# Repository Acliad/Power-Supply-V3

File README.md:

This project is for a constant voltage/constant current DC power supply designed by me. The project initially started as a way to learn more about electronics, and it served that purpose extremely well. There are many improvements that could be made, but those will probably never be realized as the next step in the Power Supply journey is a version 4 with a totally new architecture, much better mechanical design, an actually good ADC, and many more years of experience backing it.

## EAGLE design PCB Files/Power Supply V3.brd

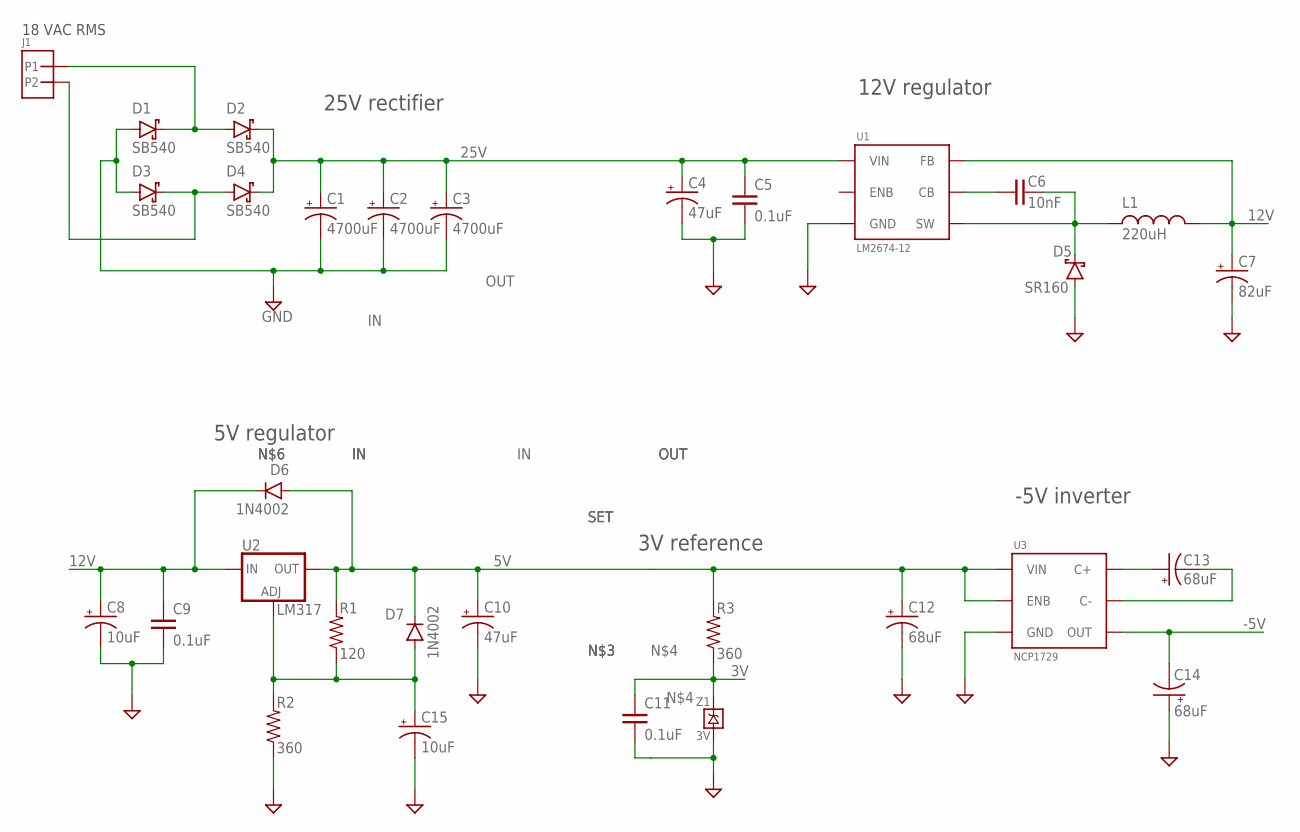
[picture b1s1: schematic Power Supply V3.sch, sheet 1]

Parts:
C1, C2, C3: 4700uF; 10MM-LEAD_22MM-DIA
C4, C10: 47uF; 2.5MM_LEAD-6.3MM_DIA
C5, C9, C11: 0.1uF; 0805
C6: 10nF; 1206
C7: 82uF; 2.5MM_LEAD-6.3MM_DIA
C8, C15: 10uF; 6032-28
C12, C13, C14: 68uF; ALUM_SMD_SMALL
D1, D2, D3, D4: SB540; DO201-15
D5: SR160; DO41-10
D6, D7: 1N4002; DO41-10
J1: MOLEX_46999-0126; 2P_MOLEX_5566
L1: 220uH; 1200LRS
R1: 120; 1/4W_0.4
R2, R3: 360; 1/4W_0.4
U1: LM2674-12; SOIC-8
U2: LM317; TO-220
U3: NCP1729; TSOP-6
Z1: 3V; TO-92_AMMO

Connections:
3V: C11.1, R3.P$1 (1), Z1.2 (V+); also elsewhere on the board
5V: C10.+, C12.+, D6.A, D7.C, R1.P$2 (2), R3.P$2 (2), U2.2 (OUT), U3.2 (VIN), U3.5 (ENB); also elsewhere on the board
12V: C7.+, C8.+, C9.1, D6.C, L1.3 (2), U1.4 (FB), U2.3 (IN); also elsewhere on the board
25V: C1.+, C2.+, C3.+, C4.+, C5.1, D2.C, D4.C, U1.7 (VIN); also elsewhere on the board
-5V: C14.-, U3.1 (OUT); also elsewhere on the board
CB: C6.1, U1.1 (CB)
GND: C1.-, C2.-, C3.-, C4.-, C5.2, C7.-, C8.-, C9.2, C10.-, C11.2, C12.-, C14.+, C15.-, D1.A, D3.A, D5.A, R2.P$1 (1), U1.6 (GND), U3.4 (GND), Z1.1 (V-); also elsewhere on the board
unnamed: D1.C, D2.A, J1.1
unnamed: D3.C, D4.A, J1.2
unnamed: C13.+, U3.6 (C+)
unnamed: C13.-, U3.3 (C-)
SET1: C15.+, D7.A, R1.P$1 (1), R2.P$2 (2), U2.1 (ADJ)
SW: C6.2, D5.C, L1.1, U1.8 (SW)

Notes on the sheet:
18 VAC RMS
25V rectifier
12V regulator
5V regulator
3V reference
-5V inverter

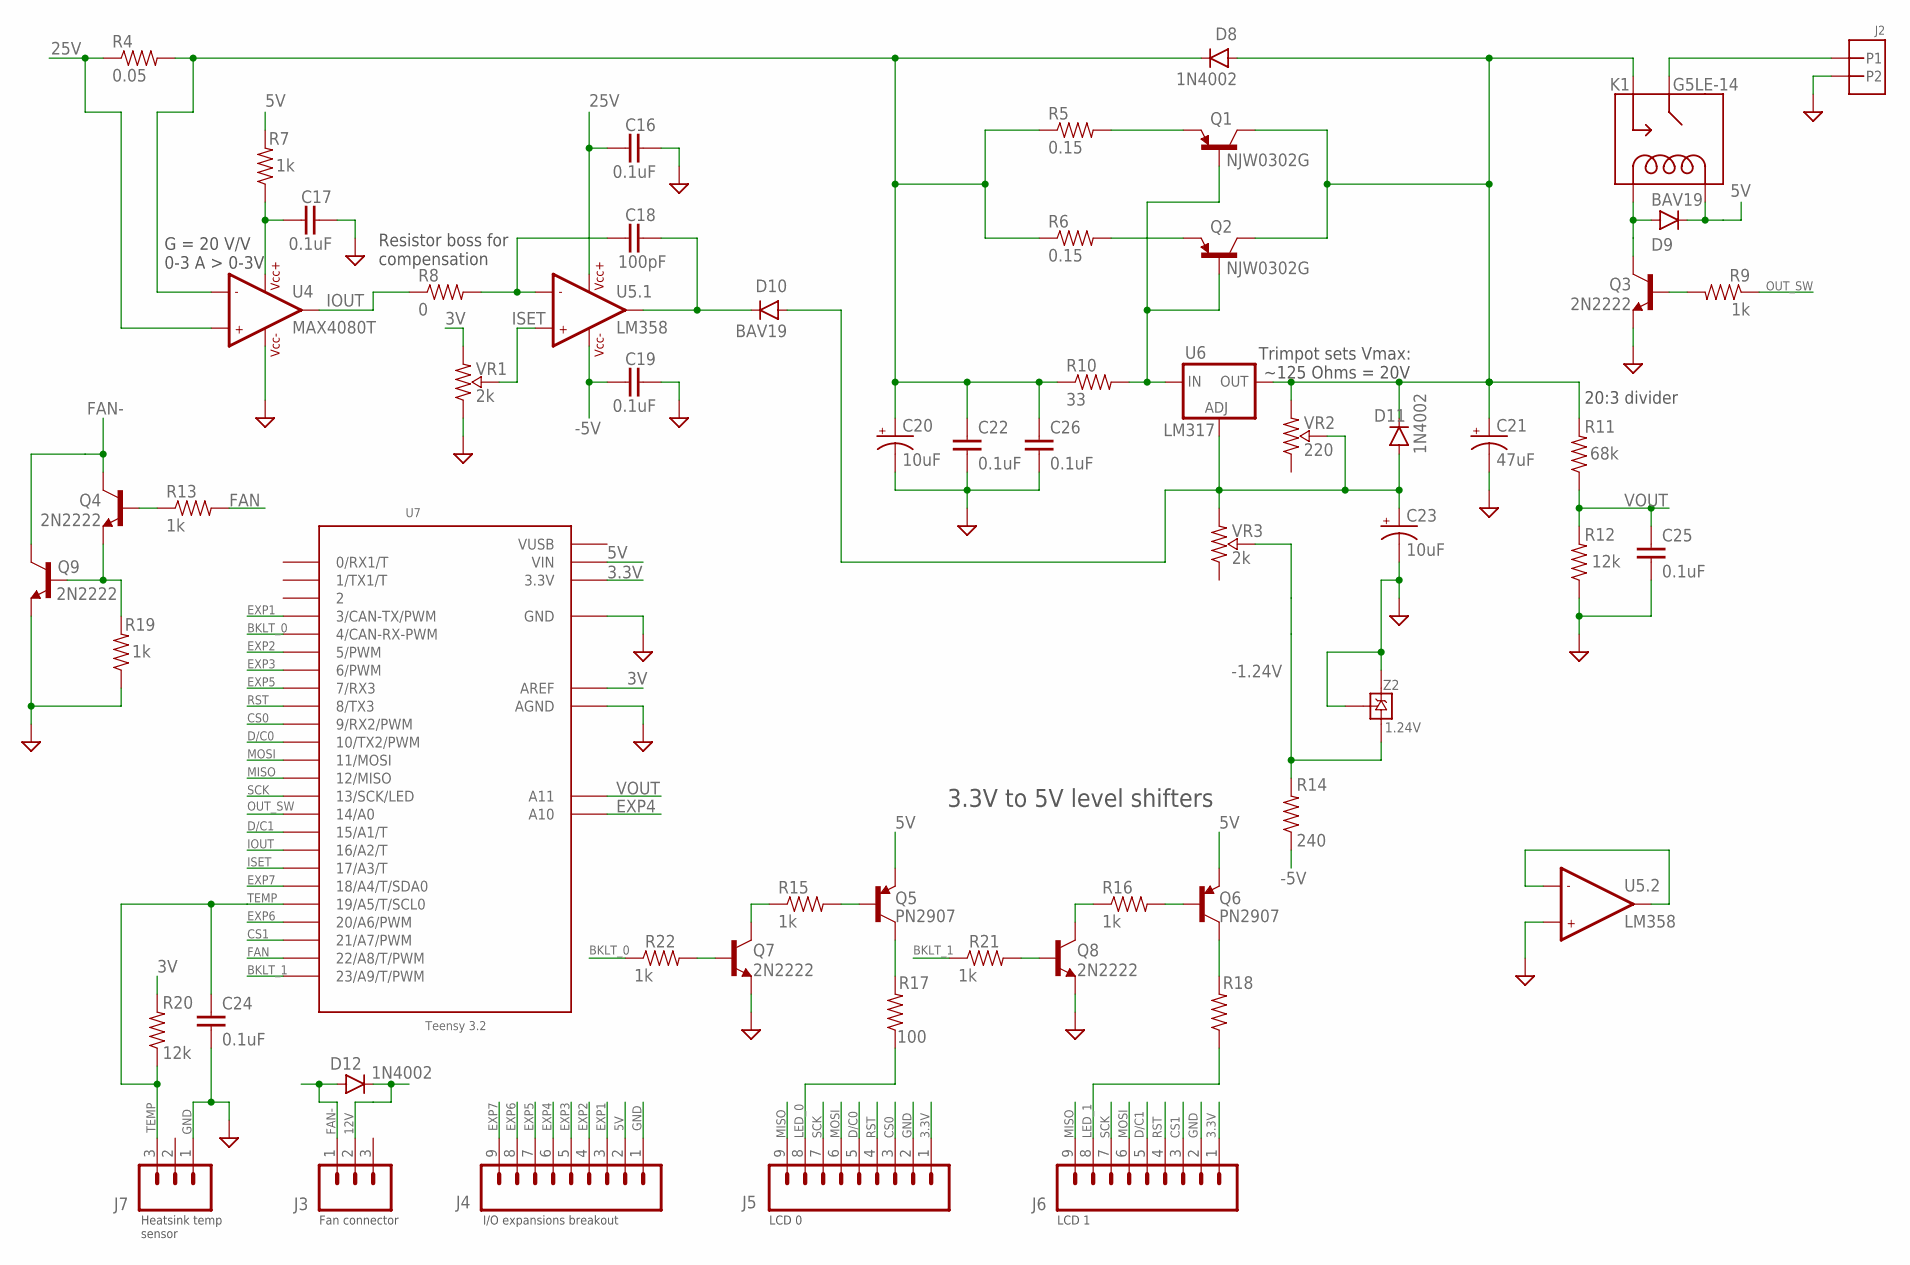
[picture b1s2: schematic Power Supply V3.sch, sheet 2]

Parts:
C16, C17, C19, C22, C24, C25, C26: 0.1uF; 0805
C18: 100pF; 2.54MM_LEAD
C20, C23: 10uF; 6032-28
C21: 47uF; 2.5MM_LEAD-6.3MM_DIA
D8, D11, D12: 1N4002; DO41-10
D9, D10: BAV19; DO35-10
J2: MOLEX_46999-0126; 2P_MOLEX_5566
J3, J7: 3P_XH2.54; XH-3P_LOCK
J4, J5, J6: 9P_XH2.54LOCK; 9P_XH2.54_LOCK
K1: G5LE-14; SPST_RELAY_NO
Q1, Q2: NJW0302G; TO-247AD-V
Q3, Q4, Q7, Q8, Q9: 2N2222; TO-92
Q5, Q6: PN2907; TO-92_AMMO
R4: 0.05; 2512
R5, R6: 0.15; 1/2W_0.5
R7, R9, R13, R15, R16, R19, R21, R22: 1k; 1/4W_0.4
R8: 0; 1/4W_0.4
R10: 33; 1/4W_0.4
R11: 68k; 0805
R12, R20: 12k; 0805
R14: 240; 1/4W_0.4
R17, R18: 100; 1/4W_0.4
U4: MAX4080T; SO08
U5: LM358; DIL-08
U6: LM317; TO-220
U7: Teensy 3.2; TEENSY3-DIL+4
VR1, VR3: 2k; XH-3P_LOCK
VR2: 220; THROUGH_HOLE_TRIMPOT
Z2: 1.24V; TO-92_AMMO

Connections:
3.3V: J5.1, J6.1, U7.3.3V
3V: R20.2, U7.AREF, VR1.3 (E); also elsewhere on the board
5V: D9.C, J4.2, K1.COIL2, Q5.1 (E), Q6.1 (E), R7.P$2 (2), U7.VIN; also elsewhere on the board
12V: D12.C, J3.2; also elsewhere on the board
25V: C16.1, R4.1, U4.1 (+IN1), U5.8 (VCC+); also elsewhere on the board
-1.24V: R14.P$2 (2), VR3.2 (S), Z2.2 (A)
-5V: C19.1, R14.P$1 (1), U5.4 (VCC-); also elsewhere on the board
BKLT_0: R22.P$1 (1), U7.4 (4/CAN-RX-PWM)
BKLT_1: R21.P$1 (1), U7.23/A9 (23/A9/T/PWM)
CS0: J5.3, U7.9 (9/RX2/PWM)
CS1: J6.3, U7.21/A7 (21/A7/PWM)
D/C0: J5.5, U7.10 (10/TX2/PWM)
D/C1: J6.5, U7.15/A1 (15/A1/T)
EXP1: J4.3, U7.3 (3/CAN-TX/PWM)
EXP2: J4.4, U7.5 (5/PWM)
EXP3: J4.5, U7.6 (6/PWM)
EXP4: J4.6, U7.A10
EXP5: J4.7, U7.7 (7/RX3)
EXP6: J4.8, U7.20/A6 (20/A6/PWM)
EXP7: J4.9, U7.18/A4 (18/A4/T/SDA0)
FAN: R13.P$2 (2), U7.22/A8 (22/A8/T/PWM)
FAN-: D12.A, J3.1, Q4.3 (C), Q9.3 (C)
GND: C16.2, C17.2, C19.2, C20.-, C21.-, C22.2, C23.-, C24.2, C25.2, C26.2, J2.2, J4.1, J5.2, J6.2, J7.1, Q3.1 (E), Q7.1 (E), Q8.1 (E), Q9.1 (E), R12.1, R19.P$1 (1), U4.4 (VCC-), U5.5 (+IN2), U7.AGND, U7.GND, VR1.1 (A), Z2.1 (REF), Z2.3 (C); also elsewhere on the board
IN: Q1.1 (B), Q2.1 (B), R10.P$2 (2), U6.3 (IN)
IOUT: R8.P$1 (1), U4.5 (OUT1), U7.16/A2 (16/A2/T)
ISET: U5.3 (+IN1), U7.17/A3 (17/A3/T), VR1.2 (S)
LED_0: J5.8, R17.P$1 (1)
LED_1: J6.8, R18.P$1 (1)
MISO: J5.9, J6.9, U7.12 (12/MISO)
MOSI: J5.6, J6.6, U7.11 (11/MOSI)
unnamed: C17.1, R7.P$1 (1), U4.2 (VCC+)
unnamed: C20.+, C22.1, C26.1, D8.C, R4.2, R5.P$1 (1), R6.P$1 (1), R10.P$1 (1), U4.8 (-IN1)
unnamed: C18.2, D10.C, U5.1 (OUT1)
unnamed: Q1.3 (E), R5.P$2 (2)
unnamed: Q2.3 (E), R6.P$2 (2)
unnamed: C18.1, R8.P$2 (2), U5.2 (-IN1)
unnamed: Q8.2 (B), R21.P$2 (2)
unnamed: J2.1, K1.COM (MAIN)
unnamed: Q7.2 (B), R22.P$2 (2)
unnamed: D9.A, K1.COIL1, Q3.3 (C)
unnamed: Q3.2 (B), R9.P$2 (2)
unnamed: Q5.3 (C), R17.P$2 (2)
unnamed: Q7.3 (C), R15.P$1 (1)
unnamed: Q6.3 (C), R18.P$2 (2)
unnamed: Q5.2 (B), R15.P$2 (2)
unnamed: Q8.3 (C), R16.P$1 (1)
unnamed: Q6.2 (B), R16.P$2 (2)
unnamed: Q4.1 (E), Q9.2 (B), R19.P$2 (2)
unnamed: Q4.2 (B), R13.P$1 (1)
OP2: U5.6 (-IN2), U5.7 (OUT2)
OUT: C21.+, D8.A, D11.C, K1.NO, Q1.2 (C), Q2.2 (C), R11.2, U6.2 (OUT), VR2.3 (E)
OUT_SW: R9.P$1 (1), U7.14/A0
RST: J5.4, J6.4, U7.8 (8/TX3)
SCK: J5.7, J6.7, U7.13 (13/SCK/LED)
SET: C23.+, D10.A, D11.A, U6.1 (ADJ), VR2.2 (S), VR3.3 (E)
TEMP: C24.1, J7.3, R20.1, U7.19/A5 (19/A5/T/SCL0)
VOUT: C25.1, R11.1, R12.2, U7.A11
VUSB: U7.VUSB

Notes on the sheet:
G = 20 V/V 0-3 A > 0-3V
Trimpot sets Vmax: ~125 Ohms = 20V
Resistor boss for compensation
20:3 divider
I/O expansions breakout
Fan connector
LCD 0
LCD 1
3.3V to 5V level shifters
Heatsink temp sensor

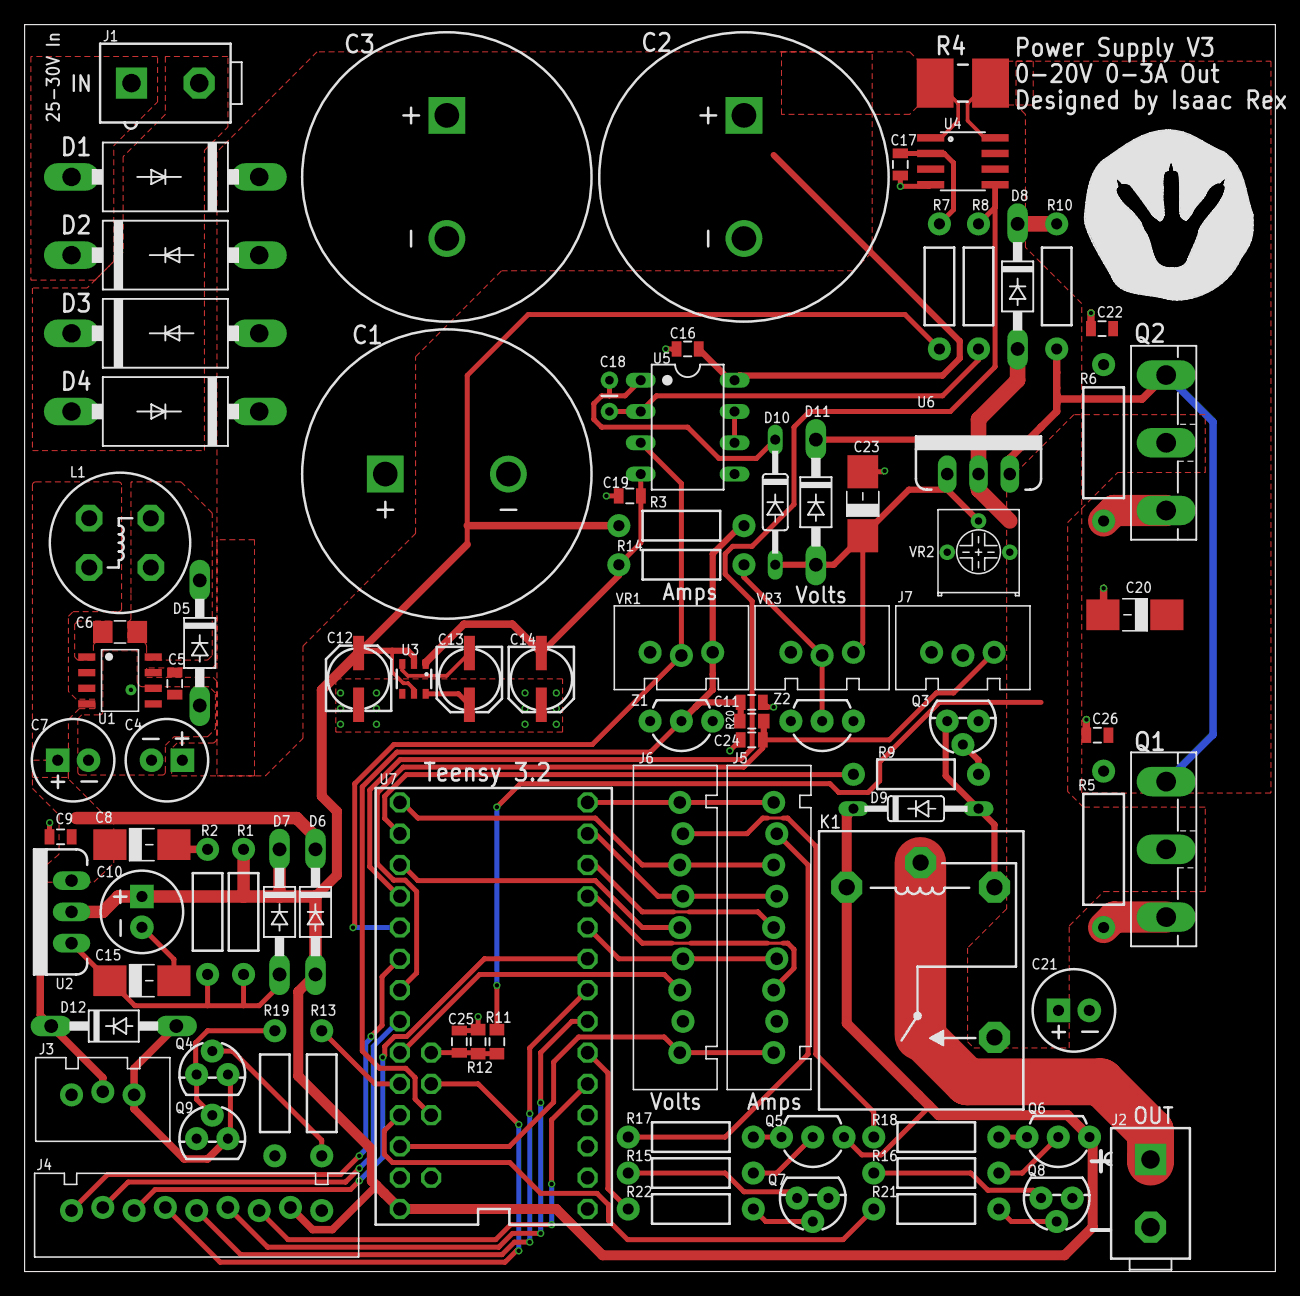
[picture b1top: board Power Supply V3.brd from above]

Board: 2 copper layers, 101.6 x 101.3 mm, 90 parts (0 on the bottom side), 64 nets.

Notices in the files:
parts and their libraries:
SparkFun-Aesthetics: Licensing: Creative Commons ShareAlike 4.0 International - https://creativecommons.org/licenses/by-sa/4.0
